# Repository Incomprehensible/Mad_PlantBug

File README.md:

# Mad_PlantBug

Low-power capacitive soil moisture sensor with BLE connectivity.

## Features

* powered via CR2032 coin battery
* transmits telemetry via BLE
* measures ambient light and temperature
* visual indication via LED

Top             |  Bottom
:-------------------------:|:-------------------------:
  |  

## How it works

This sensor determines the amount of soil moisture by measuring changes in capacitance of the probe submerged in soil.\
Insertable part forms a parasitic coplanar capacitor which uses soil as a dielectric medium.\
As the environment around the capacitor changes depending on whether the soil becomes wetter or drier, so does it capacitance.\
Together with a resistance the probe forms an RC low-pass filter.\
Changes in capacitance shape the output waveform observed by the sensor.
\
Measurement pipeline logic is as follows:\
`environment changes -> capacitance changes -> cutoff frequency changes -> peak amplitude changes`

## Capacitance measurement
* Clean PCB measurement in air: ~59pF
* Fully submerged in water: 2nF
<details><summary>Assembly & measurements</summary>

</details>

## Current issues
* CR2032 footprint and power pins connection is incorrect.

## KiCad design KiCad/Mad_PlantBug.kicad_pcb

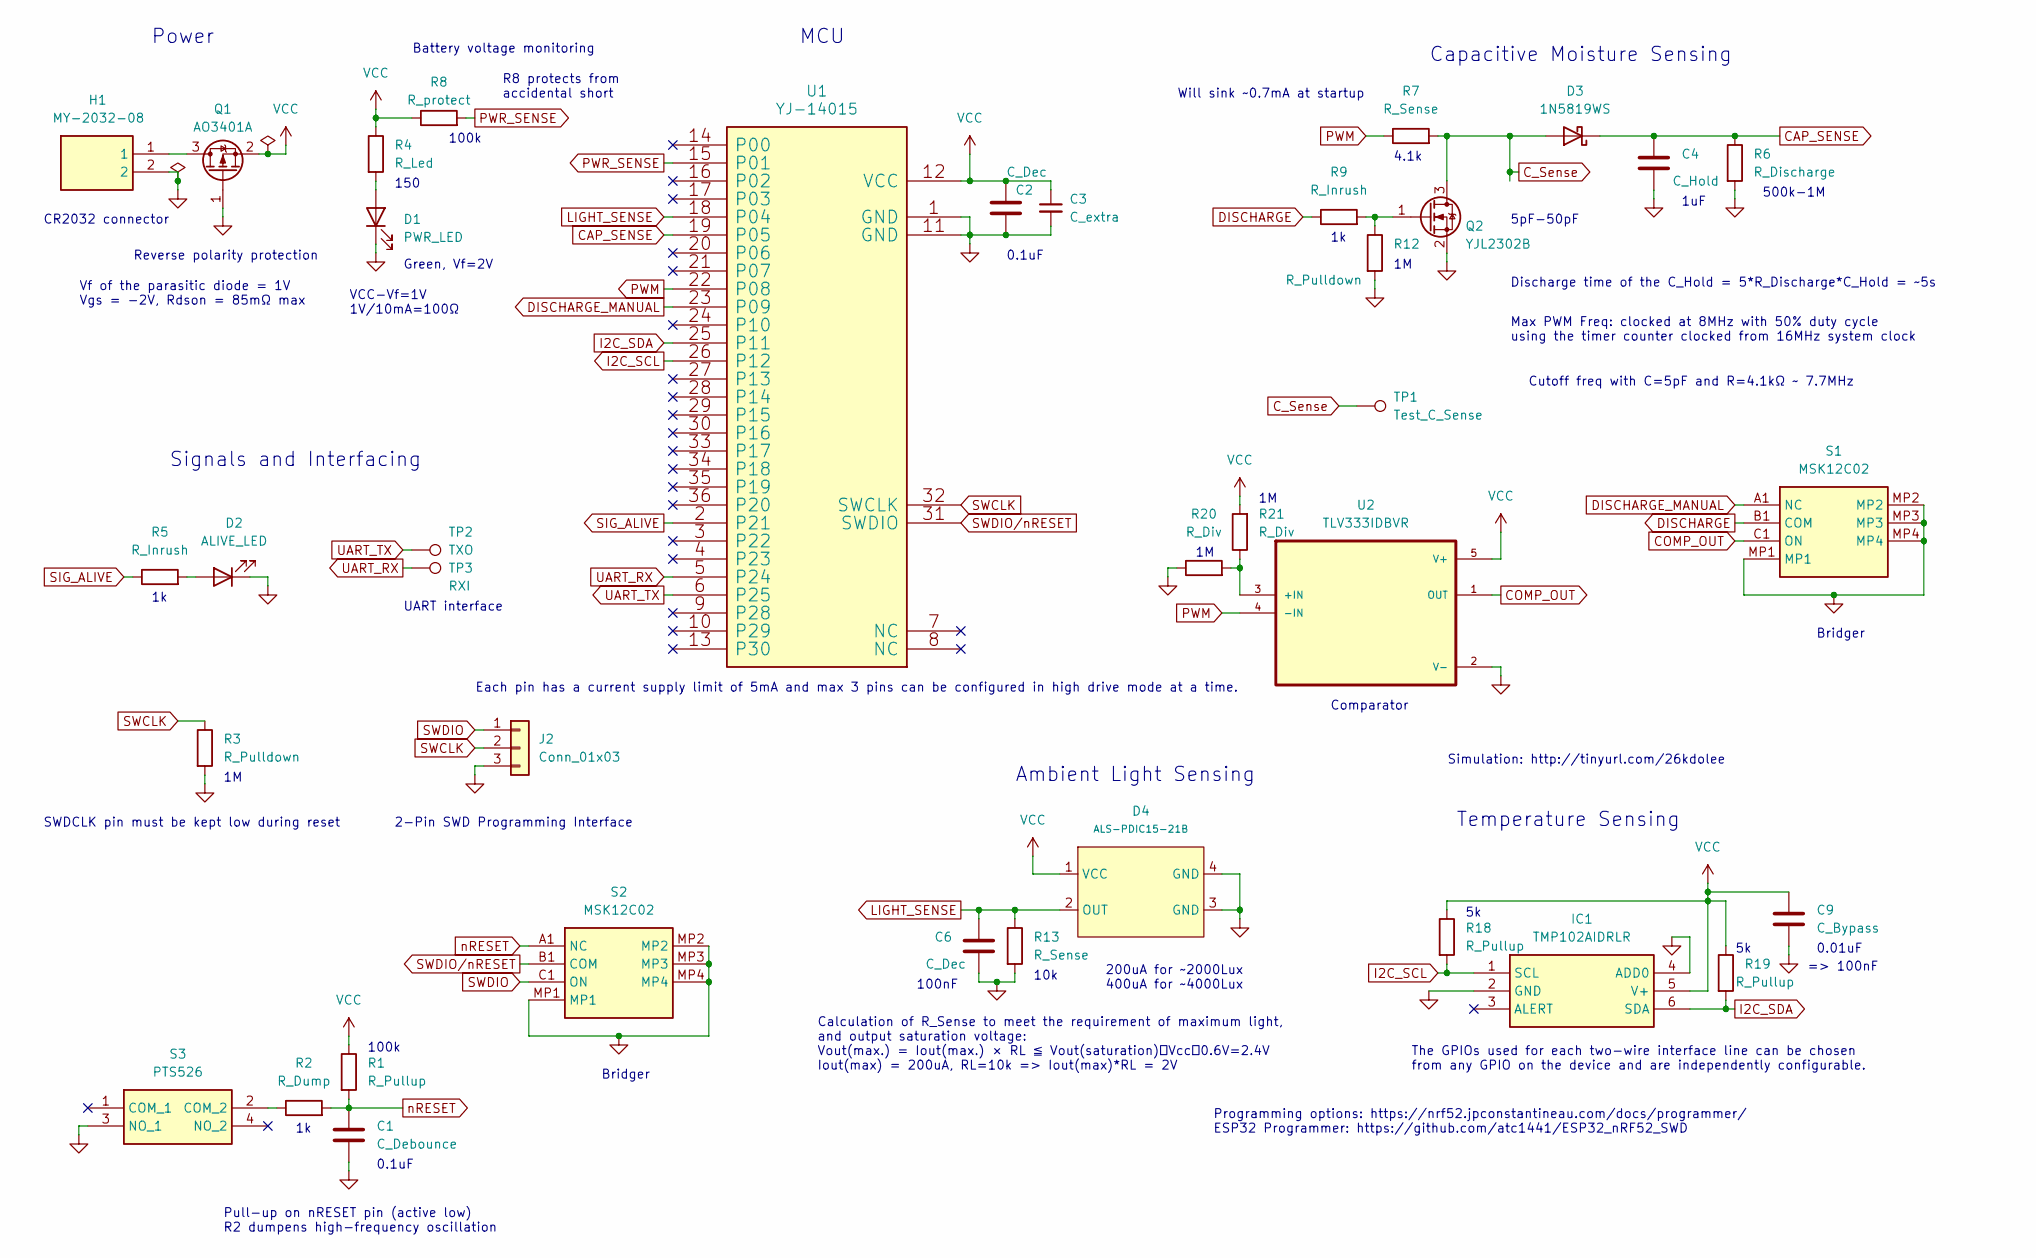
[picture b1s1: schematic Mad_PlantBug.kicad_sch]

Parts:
C1: C_Debounce; C_0603_1608Metric
C2: C_Dec; C_0603_1608Metric_Pad1.08x0.95mm_HandSolder
C3: C_extra; C_0402_1005Metric
C4: C_Hold; C_0603_1608Metric
C6: C_Dec; C_0603_1608Metric
C9: C_Bypass; C_0603_1608Metric_Pad1.08x0.95mm_HandSolder
D1: PWR_LED; LED_0603_1608Metric
D2: ALIVE_LED; LED_0603_1608Metric
D3: 1N5819WS; D_SOD-323_HandSoldering
D4: ALS-PDIC15-21B; ALS-PDIC15-21BTR8
H1: MY-2032-08; MY203208; Manufacturer_Part_Number MY-2032-08
IC1: TMP102AIDRLR; SOTFL50P160X60-6N; Manufacturer_Part_Number TMP102AIDRLR; Mouser Part Number 595-TMP102AIDRLR
J2: Conn_01x03; MOLEX_530480310
Q1: AO3401A; SOT-23
Q2: YJL2302B; SOT-23-3
R1, R18, R19: R_Pullup; R_0402_1005Metric_Pad0.72x0.64mm_HandSolder
R2: R_Dump; R_0402_1005Metric_Pad0.72x0.64mm_HandSolder
R3, R12: R_Pulldown; R_0402_1005Metric_Pad0.72x0.64mm_HandSolder
R4: R_Led; R_0402_1005Metric_Pad0.72x0.64mm_HandSolder
R5, R9: R_Inrush; R_0402_1005Metric_Pad0.72x0.64mm_HandSolder
R6: R_Discharge; R_0402_1005Metric_Pad0.72x0.64mm_HandSolder
R7: R_Sense; R_0603_1608Metric_Pad0.98x0.95mm_HandSolder
R8: R_protect; R_0402_1005Metric_Pad0.72x0.64mm_HandSolder
R13: R_Sense; R_0402_1005Metric_Pad0.72x0.64mm_HandSolder
R20, R21: R_Div; R_0402_1005Metric_Pad0.72x0.64mm_HandSolder
S1, S2: MSK12C02; Manufacturer_Part_Number MSK12C02
S3: PTS526; PTS526SK15SMTR2LFS; Manufacturer_Part_Number PTS526 SK15 SMTR2 LFS; Mouser Part Number 611-PTS526SK15SMR2L
TP1: Test_C_Sense; TestPoint_Pad_1.0x1.0mm
TP2: TXO; TestPoint_Pad_1.0x1.0mm
TP3: RXI; TestPoint_Pad_1.0x1.0mm
U1: YJ-14015; YJ-14015-Module
U2: TLV333IDBVR; TLV333-SOT95P280X145-5N

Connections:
CAP_SENSE: C4.1, D3.1 (K), R6.1, U1.19 (P05)
COMP_OUT: S1.C1 (ON), U2.1 (OUT)
C_Sense: D3.2 (A), Q2.3 (D), R7.2, TP1.1
DISCHARGE: R9.1, S1.B1 (COM)
DISCHARGE_MANUAL: S1.A1 (NC), U1.23 (P09)
GND: C1.2, C2.2, C3.2, C4.2, C6.2, C9.2, D1.1 (K), D2.1 (K), D4.3 (GND), D4.4 (GND), H1.2, IC1.2 (GND), IC1.4 (ADD0), J2.3, Q1.1 (G), Q2.2 (S), R3.2, R6.2, R12.2, R13.2, R20.1, S1.MP1, S1.MP2, S1.MP3, S1.MP4, S2.MP1, S2.MP2, S2.MP3, S2.MP4, S3.3 (NO_1), U1.1 (GND), U1.11 (GND), U2.2 (V-)
I2C_SCL: IC1.1 (SCL), R18.2, U1.26 (P12)
I2C_SDA: IC1.6 (SDA), R19.2, U1.25 (P11)
LIGHT_SENSE: C6.1, D4.2 (OUT), R13.1, U1.18 (P04)
unnamed: D1.2 (A), R4.2
unnamed: D2.2 (A), R5.2
unnamed: H1.1, Q1.3 (D)
unnamed: Q2.1 (G), R9.2, R12.1
unnamed: R2.1, S3.2 (COM_2)
unnamed: R20.2, R21.1, U2.3 (+IN)
PWM: R7.1, U1.22 (P08), U2.4 (-IN)
PWR_SENSE: R8.2, U1.15 (P01)
SIG_ALIVE: R5.1, U1.2 (P21)
SWCLK: J2.2, R3.1, U1.32 (SWCLK)
SWDIO: J2.1, S2.C1 (ON)
SWDIO/nRESET: S2.B1 (COM), U1.31 (SWDIO)
UART_RX: TP3.1, U1.5 (P24)
UART_TX: TP2.1, U1.6 (P25)
VCC: C2.1, C3.1, C9.1, D4.1 (VCC), IC1.5 (V+), Q1.2 (S), R1.1, R4.1, R8.1, R18.1, R19.1, R21.2, U1.12 (VCC), U2.5 (V+)
nRESET: C1.1, R1.2, R2.2, S2.A1 (NC)

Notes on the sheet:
Simulation: http://tinyurl.com/26kdolee
MCU
100k
Cutoff freq with C=5pF and R=4.1kΩ ~ 7.7MHz
Bridger
0.1uF
500k-1M
CR2032 connector
SWDCLK pin must be kept low during reset
Battery voltage monitoring
VCC-Vf=1V 1V/10mA=100Ω
Ambient Light Sensing
100nF
Pull-up on nRESET pin (active low) R2 dumpens high-frequency oscillation
Green, Vf=2V
0.01uF
150
4.1k
Discharge time of the C_Hold = 5*R_Discharge*C_Hold = ~5s
Calculation of R_Sense to meet the requirement of maximum light, and output saturation voltage: Vout(max.) = Iout(max.) × RL ≦ Vout(saturation)＝Vcc－0.6V=2.4V Iout(max) = 200uA, RL=10k => Iout(max)*RL = 2V
R8 protects from accidental short
Vf of the parasitic diode = 1V Vgs = -2V, Rdson = 85mΩ max
5pF-50pF
Reverse polarity protection
Power
The GPIOs used for each two-wire interface line can be chosen from any GPIO on the device and are independently configurable.
1uF
Capacitive Moisture Sensing
Temperature Sensing
Will sink ~0.7mA at startup
Max PWM Freq: clocked at 8MHz with 50% duty cycle using the timer counter clocked from 16MHz system clock
10k
Each pin has a current supply limit of 5mA and max 3 pins can be configured in high drive mode at a time.
Comparator
200uA for ~2000Lux 400uA for ~4000Lux
2-Pin SWD Programming Interface
=> 100nF
Signals and Interfacing
Programming options: https://nrf52.jpconstantineau.com/docs/programmer/ ESP32 Programmer: https://github.com/atc1441/ESP32_nRF52_SWD
UART interface

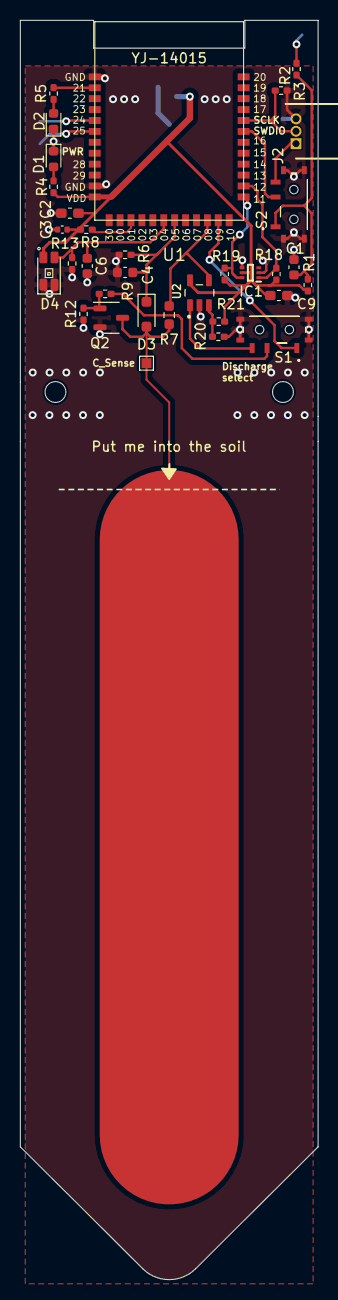
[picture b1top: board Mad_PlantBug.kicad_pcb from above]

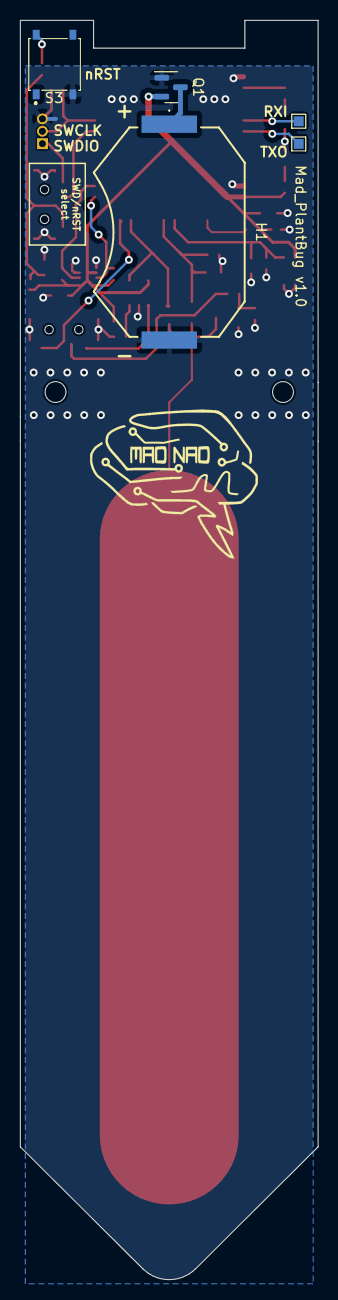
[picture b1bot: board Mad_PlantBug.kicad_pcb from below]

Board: 2 copper layers, 30.0 x 126.9 mm, 38 parts (5 on the bottom side), 25 nets.

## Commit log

2024-02-17 Added first version of schematics with old symbols for some components.
2024-02-22 Last version of the full schematics with all assigned footprints. Added simulaion sheet.
2024-02-25 Finished schematics, layed out the components, added ADC battery voltage input, defined board outline, traced a sensor capacitor.
2024-02-28 First version of the sensor is up.
2024-02-28 Updated README.
2024-02-28 Added schematics pdf.
2024-02-28 Routed UART, added some designators, added gerbers.
2024-02-29 Updated schematics pdf.
2024-10-14 Added empirical measurements + pictures.
